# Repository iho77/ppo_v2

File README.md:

Shield: [![CC BY-NC 4.0][cc-by-nc-shield]][cc-by-nc]

This work is licensed under a
[Creative Commons Attribution-NonCommercial 4.0 International License][cc-by-nc].

[![CC BY-NC 4.0][cc-by-nc-image]][cc-by-nc]

[cc-by-nc]: https://creativecommons.org/licenses/by-nc/4.0/
[cc-by-nc-image]: https://licensebuttons.net/l/by-nc/4.0/88x31.png
[cc-by-nc-shield]: https://img.shields.io/badge/License-CC%20BY--NC%204.0-lightgrey.svg

# PPO2 Display

A high-precision Partial Pressure of Oxygen (PPO2) monitoring system for technical diving, built on ESP32-C3 with dual O2 sensor support and advanced signal processing algorithms.

## Safety Notes

⚠️ **WARNING**:

OXYGEN PPO MONITORING SOFTWARE

This software is not a dive computer, life-support system, medical device, or safety-critical instrument. It is provided for informational and educational purposes only. Readings may be inaccurate, delayed, or fail due to sensor drift/aging, moisture, calibration error, power or hardware faults, electromagnetic interference, or software bugs.

Do not rely on this software to determine breathing-gas safety. Always follow certified dive training and procedures, use approved equipment, carry independent/redundant instruments, and maintain conservative dive plans. Diving—especially with rebreathers—carries inherent risks of serious injury or death.

The software is provided “AS IS,” without warranties of any kind. To the maximum extent permitted by law, the developer disclaims all liability for any loss, damage, injury, or death arising from use or misuse of this software. By downloading, installing, or using the software, you acknowledge and accept all risks and agree to release, indemnify, and hold the developer harmless from any claims.

If you do not agree, do not use this software.

⚠️ **IMPORTANT**: This sostware developed  using Anthropic Claude heavly with lack of human verification and testing.  

⚠️ **IMPORTANT**: This system is designed for TESTING PURPUSES ONLY. Users must:

1. **Validate Calibration**: Always verify calibration with known gas mixtures
2. **Dual Sensor Monitoring**: Never dive with single sensor operation
3. **Regular Maintenance**: Check sensor health and calibration frequently
4. **Backup Systems**: Always carry independent PPO2 monitoring
5. **Training Required**: Proper technical diving certification essential

This system is a diving aid and should not be the sole method of gas monitoring during technical dives.

## Required Tools & Environment

  - ESP-IDF Framework - Espressif's official development framework
  - CMake (3.16+) - Build system
  - Python - For ESP-IDF tools and flashing
  - Git - For version control and ESP-IDF installation

## Hardware Platform

  - Target MCU: ESP32-C3 Development Board
  - Display: 128x128 SH1107 OLED (I2C at 0x3D, 400kHz)
  - Sensors: Internal ADC for O2 sensor readings
  - Buttons: 2x GPIO buttons (MODE/SELECT)
  - LED: Built-in RGB LED for warnings

## Key Libraries & Components

  - FreeRTOS - Real-time operating system (1kHz tick)
  - ESP-IDF I2C Master Driver - Hardware communication
  - NVS Flash - Non-volatile storage for configuration
  - ESP Task Watchdog - System safety monitoring
  - Custom Components:
    - Display Manager (SH1107 driver)
    - Sensor Manager (O2 sensor interface)
    - Button Manager (GPIO with debouncing)
    - Warning Manager (LED control)
    - PPO2 Logger (data logging)

### Pin Configuration
```
GPIO 0  -> ADC1_CH0 (O2 Sensor 1)
GPIO 1  -> ADC1_CH1 (O2 Sensor 2) 
GPIO 3  -> ADC1_CH3 (Battery voltage divider 1/3)
GPIO 6  -> I2C SDA (Display)
GPIO 7  -> I2C SCL (Display)
GPIO 5  -> MODE Button
GPIO 10  -> SELECT Button
GPIO 8  -> RGB LED (Warning system)
```

## Key Features

### Sensor Management
- **Dual O2 Sensor Support**: Independent sensor processing with disagreement detection
- **Single sensor auto detection**: Short  Sensor + in cable connector to ground - device starts to work in 1 sensor modeI
- **Multipoint Calibration System**: Air (21%), O2 (100%) or custom mix calibration points
- **Advanced Signal Processing**: Median-of-5 → EMA → Slew-rate limiting pipeline
- **Sensor Health Monitoring**: Automatic failure detection and recovery
- **Battery Monitoring**: Real-time voltage and percentage display

### Display System
- **Main Display**: Large PPO2 values with calibration status indicators
- **Warning System**: Scrolling text warnings with LED color coding
- **Battery Display**: Dynamic battery icon with voltage readout
- **Menu System**: Clean navigation with visual selection indicators

### Warning System
- **PPO2 Thresholds**: Configurable low/high warning and alarm levels
- **Sensor Disagreement**: Automatic detection of sensor variance
- **Visual Alerts**: Color-coded LED (Green/Yellow/Red) with blinking patterns
- **Display Integration**: Warning messages shown on main screen

## Core Algorithms

### 1. Robust Signal Processing Pipeline

The system implements a sophisticated 3-stage filtering pipeline for each O2 sensor:

Use 3 stages: spike removal → low-pass → rate limit + debounced alarms.

Spike/outlier killer (median-of-5)
At each 20 Hz step, keep the last 5 raw samples and take the median.

Purpose: remove single-sample glitches without adding much lag (~0.1–0.15 s).

Exponential moving average (EMA) with ~5 s time constant
Let y[n] = y[n−1] + α (x_med[n] − y[n−1]), where x_med is from step 1.

Sampling period dt = 1/20 = 0.05 s.

Choose time constant τ ≈ 5 s → α = dt/τ = 0.05/5 = 0.01.

Why: 5 s LPF kills high-freq jitter while keeping latency modest (~τ behind fast ramps).

Slew-rate limiter (enforce physics)
If the environment cannot change by more than Δ_meaningful per 10 s, set

S_max = Δ_meaningful / 10 (units per second).

Per-sample limit: Δ_per_sample = S_max * dt.
Then clamp the EMA output change:
y_lim[n] = clamp(y[n−1] − Δ_per_sample, y[n], y[n−1] + Δ_per_sample).

Purpose: guarantees your displayed value can’t “move” faster than reality.

Debounced, hysteretic warnings (no flicker)

Trigger threshold: T_hi. Clear threshold: T_lo (with T_lo closer to normal than T_hi → hysteresis gap).

Require persistence: only raise a warning if y_lim[n] > T_hi continuously for T_confirm (e.g., 2–3 s).

Only clear if y_lim[n] < T_lo continuously for T_clear (e.g., 2–3 s).

Implement with two counters that increment while condition holds and reset otherwise.

That stack is O(1) memory and CPU, super stable, and easy to tune.

### 2. Multipoint Calibration System

Replaces traditional linear calibration with a robust 1 or 2-point system:

#### Calibration Points
1. **Air Calibration** (21% O2 at 1 bar): `PPO2 = 0.21 bar`
2. **Oxygen Calibration** (100% O2 at 1 bar): `PPO2 = 1.00 bar`
2. **Custom mix Calibration** (Custom % O2 at 1 bar)

System can works with 1 point calibration or 2 points calibration. In case of 1 point calibration second point is 0 mv\ 0% oxygen.

### 3. Sensor Health Monitoring

#### Health Checks
1. **Voltage Range Validation**: 0-1000mV acceptable range
2. **Calibration Validity**: Both sensors must have valid calibration
3. **Sensor Disagreement**: PPO2 difference > 0.05 bar triggers warning
4. **Communication Errors**: ADC read failures tracked and recovered

# Calibration-Based Drift & Linearity Tracking (Strategy 1)

A clear, hands-on guide you can mirror in logs, a spreadsheet, or firmware notes.

## What you track (per sensor)

* **Gain / sensitivity `k`** (mV/ata): millivolts per 1.0 ata ppO₂.
* **Offset `b`** (mV): reading at ppO₂ = 0 (should be near 0).
* **Normalized sensitivity `S = k / k₀`** vs **new-sensor baseline** `k₀`.
* **Linearity** across multiple known ppO₂ points: **`R²`** and **max residual** (mV).
* **Drift rate** (e.g., %/month) and **predicted EOL** date (when `S` hits your fail threshold, e.g., `0.70`).

---

## Two-Point Calibration (minimum viable)

At each calibration, expose the sensor to two **known** ppO₂ points and record:

* `(p₁, m₁)`: e.g., **air at surface** → `p₁ ≈ 0.209` ata, measured `m₁` (mV)
* `(p₂, m₂)`: e.g., **100% O₂ at surface** → `p₂ = 1.00` ata, measured `m₂` (mV)

Fit a line `m = k·p + b`:

```
k = (m₂ − m₁) / (p₂ − p₁)
b = m₁ − k · p₁
```

Then compute **normalized sensitivity**:

```
S = k / k₀
```

Where `k₀` is your **new-sensor baseline** (mV/ata).

---

## Worked Example A — two-point checks over time (one sensor)

Assume `k₀ = 52.0` mV/ata (≈ 11 mV in air, ≈ 52 mV at 1.0 ata O₂).

| Date       | Air mV `m₁` | O₂ mV `m₂` | Estimated `k` (mV/ata) | `b` (mV) | `S = k/k₀` |
| ---------- | ----------: | ---------: | ---------------------: | -------: | ---------: |
| 2025-01-01 |       10.99 |      52.25 |                  52.16 |     0.09 |      1.003 |
| 2025-05-01 |       10.45 |      49.51 |                  49.37 |     0.14 |      0.950 |
| 2025-10-01 |        9.48 |      45.86 |                  46.00 |    −0.14 |      0.885 |
| 2026-03-01 |        8.18 |      39.82 |                  39.99 |    −0.18 |      0.769 |

### Interpretation

* Sensitivity `S` drifts from \~1.00 → 0.77 over \~14 months (≈ 1.6 %/month).
* **Caution** when `S < 0.80` (here: 2026-03-01).
* **Predict EOL** when `S` hits **0.70**: extrapolation from the last trend ≈ **Aug 2026** (\~19 months from first calibration).

**Log each time:** the two mV readings and the computed `k`, `b`, `S`, plus a trendline of `S` vs time (and ETA to `S = 0.70`).

---

## Practical guardrails

* If `|b| > 2–3` mV or it drifts steadily, investigate (zero-current leakage, moisture, wiring).
* If degradation accelerates (> \~3–5 %/month), plan an early swap.

#### Failure Recovery
- **Graceful Degradation**: System continues with single sensor
- **Fail-Safe PPO2**: Conservative 0.21 bar default during total failure
- **Automatic Recovery**: Sensors re-validated on successful reads

### 4. Warning State Machine

#### Warning States
```c
typedef enum {
    WARNING_STATE_NORMAL = 0,    // Green LED - PPO2 in range
    WARNING_STATE_WARNING,       // Yellow blinking - PPO2 at limits  
    WARNING_STATE_ALARM         // Red blinking - PPO2 dangerous
} warning_state_t;
```

#### PPO2 Thresholds (Configurable)
- **Low Warning**: 0.19 bar (hypoxia risk)
- **Low Alarm**: 0.18 bar (severe hypoxia)
- **High Warning**: 1.4 bar (oxygen toxicity risk)
- **High Alarm**: 1.6 bar (severe toxicity risk)

#### LED Patterns
- **Normal**: Solid green
- **Warning**: Yellow blink at 2Hz (250ms on/off)
- **Alarm**: Red blink at 4Hz (125ms on/off)

## System Architecture

### Component Organization
```
├── main/                   # Main application and mode management
│   ├── main.c             # System initialization and 20Hz main loop
│   └── modes/             # Mode-specific implementations
├── components/
│   ├── app_common/        # Shared types and configuration
│   ├── sensor_manager/    # O2 sensor processing and calibration
│   ├── display_manager/   # LVGL display driver and UI
│   ├── warning_manager/   # LED warning system
│   ├── button_manager/    # GPIO button handling
│   └── sh1107_driver/     # Low-level display driver
```

### Data Flow
```
Sensors (20Hz) → Filtering → Calibration → Warning Analysis → Display Update
                     ↓
              Health Monitoring → Recovery Actions
```

## Menu System

### Main Menu Items
1. **Sensor Calibration** - Dual sensor calibration with gas selection
2. **Reset Calibration** - Individual or bulk calibration reset
3. **Print Logs** - Debug output to serial console
4. **Sensor Health** - Real-time sensor diagnostics
5. **System Setup** - Configuration and thresholds
6. **Power Off** - System shutdown

### Calibration Workflow
1. **Gas Selection**: Air, O2, or Custom (configurable %)
2. **Dual Sensor Display**: Live mV readings for both sensors
3. **Calibration Action**: Simultaneous calibration of both sensors
4. **Validation**: Automatic sanity checks and confirmation

### Setup Options
- **PPO2 Thresholds**: Warning and alarm levels for low/high PPO2
- **Display Settings**: Brightness and contrast
- **Sensor Configuration**: Individual sensor enable/disable
- **System Parameters**: Sample rates and filter constants

## Technical Specifications

### Performance
- **Update Rate**: 20 Hz sensor sampling and display refresh
- **Response Time**: ~5 seconds (90% settling due to EMA filtering)
- **Accuracy**: ±0.01 bar PPO2 (post-calibration)
- **Resolution**: 12-bit ADC (0.25mV resolution)

## Contributing

Contributions welcome! Please read CONTRIBUTING.md for guidelines on:
- Code style and standards
- Testing requirements
- Safety considerations for diving equipment

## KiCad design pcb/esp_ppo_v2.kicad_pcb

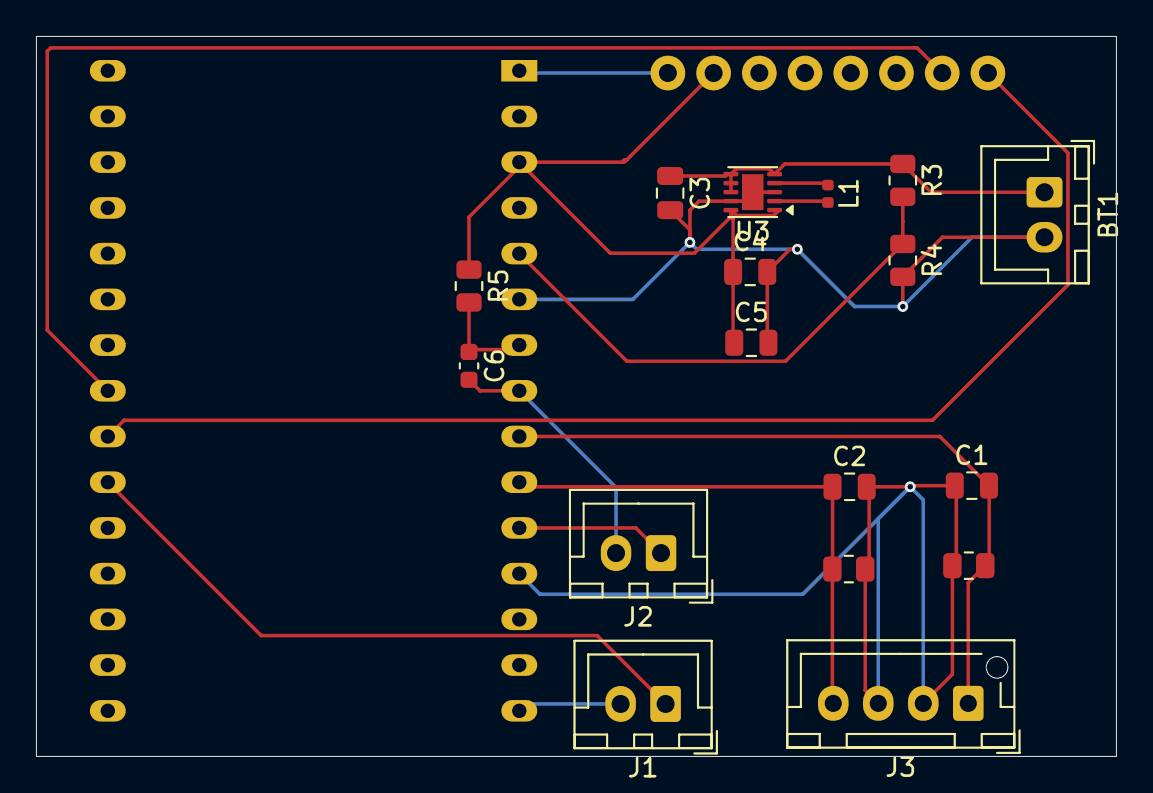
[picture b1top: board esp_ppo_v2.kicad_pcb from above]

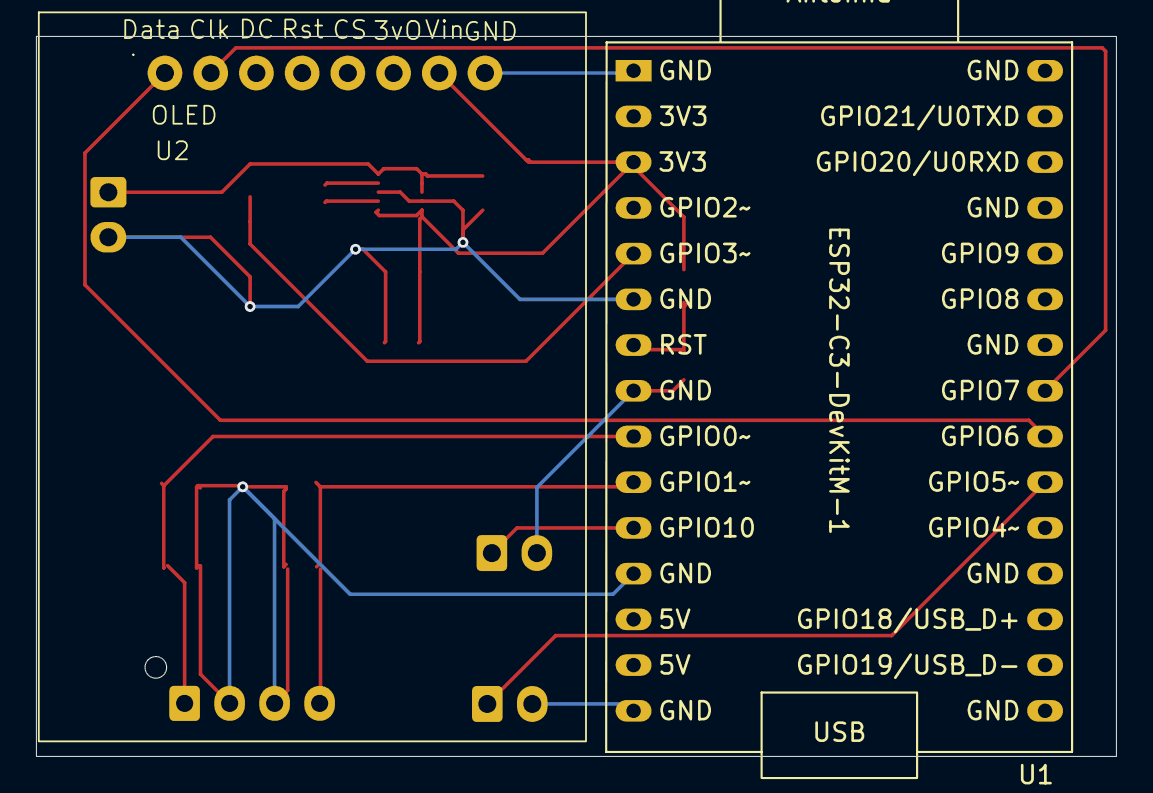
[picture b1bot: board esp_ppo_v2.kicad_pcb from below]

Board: 2 copper layers, 60.0 x 40.0 mm, 19 parts (2 on the bottom side), 13 nets.

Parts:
BT1: Battery; JST_XH_B2B-XH-A_1x02_P2.50mm_Vertical
C1, C2: 1uF; C_0805_2012Metric
C3: 4.7uF; C_0805_2012Metric
C4, C5: 10uF; C_0805_2012Metric
C6: 10uF; C_0603_1608Metric
J1, J2: Conn_01x02_Socket; JST_XH_B2B-XH-A_1x02_P2.50mm_Vertical
J3: Conn_01x04_Socket; JST_XH_B4B-XH-AM_1x04_P2.50mm_Vertical
L1: 1.5uH; L_0402_1005Metric
R1, R2: 10K; R_0805_2012Metric
R3: 200k; R_0805_2012Metric
R4: 100K; R_0805_2012Metric
R5: 10k; R_0805_2012Metric
U1: ESP32-C3-DevKitM-1
U2: 128x128_OLED
U3: TPS63031DSK; WSON-10-1EP_2.5x2.5mm_P0.5mm_EP1.2x2mm

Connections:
+3.3V: C4.1, C5.1, R5.1, U1.2 (3V3), U1.3 (3V3), U2.7 (Vin), U3.1 (VOUT), U3.10 (FB)
+BATT: BT1.1 (+), C3.1, R3.1, U3.5 (VIN), U3.6 (EN), U3.7 (PS/SYNC), U3.8 (VINA)
ADC_1: C2.1, J3.4, R2.1, U1.10 (GPIO1)
ADC_2: C1.2, J3.1, R1.2, U1.9 (GPIO0)
ADC_BAT: R3.2, R4.1, U1.5 (GPIO3)
BTN-M: J1.1, U1.21 (GPIO5)
BTN-S: J2.1, U1.11 (GPIO10)
GND: BT1.2 (-), C1.1, C2.2, C3.2, C4.2, C5.2, C6.2, J1.2, J2.2, J3.2, J3.3, R1.1, R2.2, R4.2, U1.1 (GND), U1.6 (GND), U1.8 (GND), U1.12 (GND), U1.15 (GND), U1.16 (GND), U1.19 (GND), U1.24 (GND), U1.27 (GND), U1.30 (GND), U2.8 (GND), U3.3 (PGND), U3.9 (GND), U3.11 (PGND)
unnamed: C6.1, R5.2, U1.7 (RST)
unnamed: L1.1, U3.4 (L1)
unnamed: L1.2, U3.2 (L2)
SCL: U1.23 (GPIO7), U2.2 (Clk)
SDA: U1.22 (GPIO6), U2.1 (Data)

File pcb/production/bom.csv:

Designator,Footprint,Quantity,Value,LCSC Part #
BT1,JST_XH_B2B-XH-A_1x02_P2.50mm_Vertical,1,Battery,C7429632
"C1, C2",0805,2,1uF,C24123
C3,0805,1,4.7uF,C107365
"C4, C5",0805,2,10uF,C1713
"J1, J2",JST_XH_B2B-XH-A_1x02_P2.50mm_Vertical,2,Conn_01x02_Socket,C7429632
J3,JST_XH_B4B-XH-AM_1x04_P2.50mm_Vertical,1,Conn_01x04_Socket,
L1,0402,1,1.5uH,C6364721
"R1, R2",0805,2,10K,C17414
R3,0805,1,200k,C149504
R4,0805,1,100K,C2907238
U3,WSON-10-1EP_2.5x2.5mm_P0.5mm_EP1.2x2mm,1,TPS63031DSK,C15516

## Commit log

2025-09-13 add setup for warnings treshhold and improve raw sesnor readings
2025-09-14 change atten
2025-09-15 gpio optimisation
2025-09-15 different attens for battery and sensor adc channels
2025-09-15 minor startup screen update
2025-09-16 improvements to main loop by Codex
2025-09-16 display update policy
2025-09-16 single sensor mode detection
2025-09-16 readme update
2025-09-18 voltage divider ratio update
2025-09-19 Major issue with 2 point calibration correction. Some stack overflow during logging corrected
2025-09-19 add circuit.png
2025-09-20 get rid of float math as much as possible
2025-09-21 power friom battery alligments
2025-09-22 get rid of float point operations in sensor management. Simplify filtering
2025-09-22 battery bias adc channel corrected
2025-09-23 Power consumption optimization
2025-09-24 Depricated code clean up
2025-09-24 float ops minimalization
2025-09-25 float operations clean up
2025-10-08 deep sleep if battery < 2.8
2025-10-13 adjustments to CR2 battery
2025-10-21 new CR2 battery start up issues
2025-11-01 KiCad PCB
2025-11-06 Button issues clean-up
2025-11-06 average window increase
2025-11-06 switch from mv to ADC readings in ppo calc for precision
2025-11-06 filter adjustments
2025-11-06 battery cut off
